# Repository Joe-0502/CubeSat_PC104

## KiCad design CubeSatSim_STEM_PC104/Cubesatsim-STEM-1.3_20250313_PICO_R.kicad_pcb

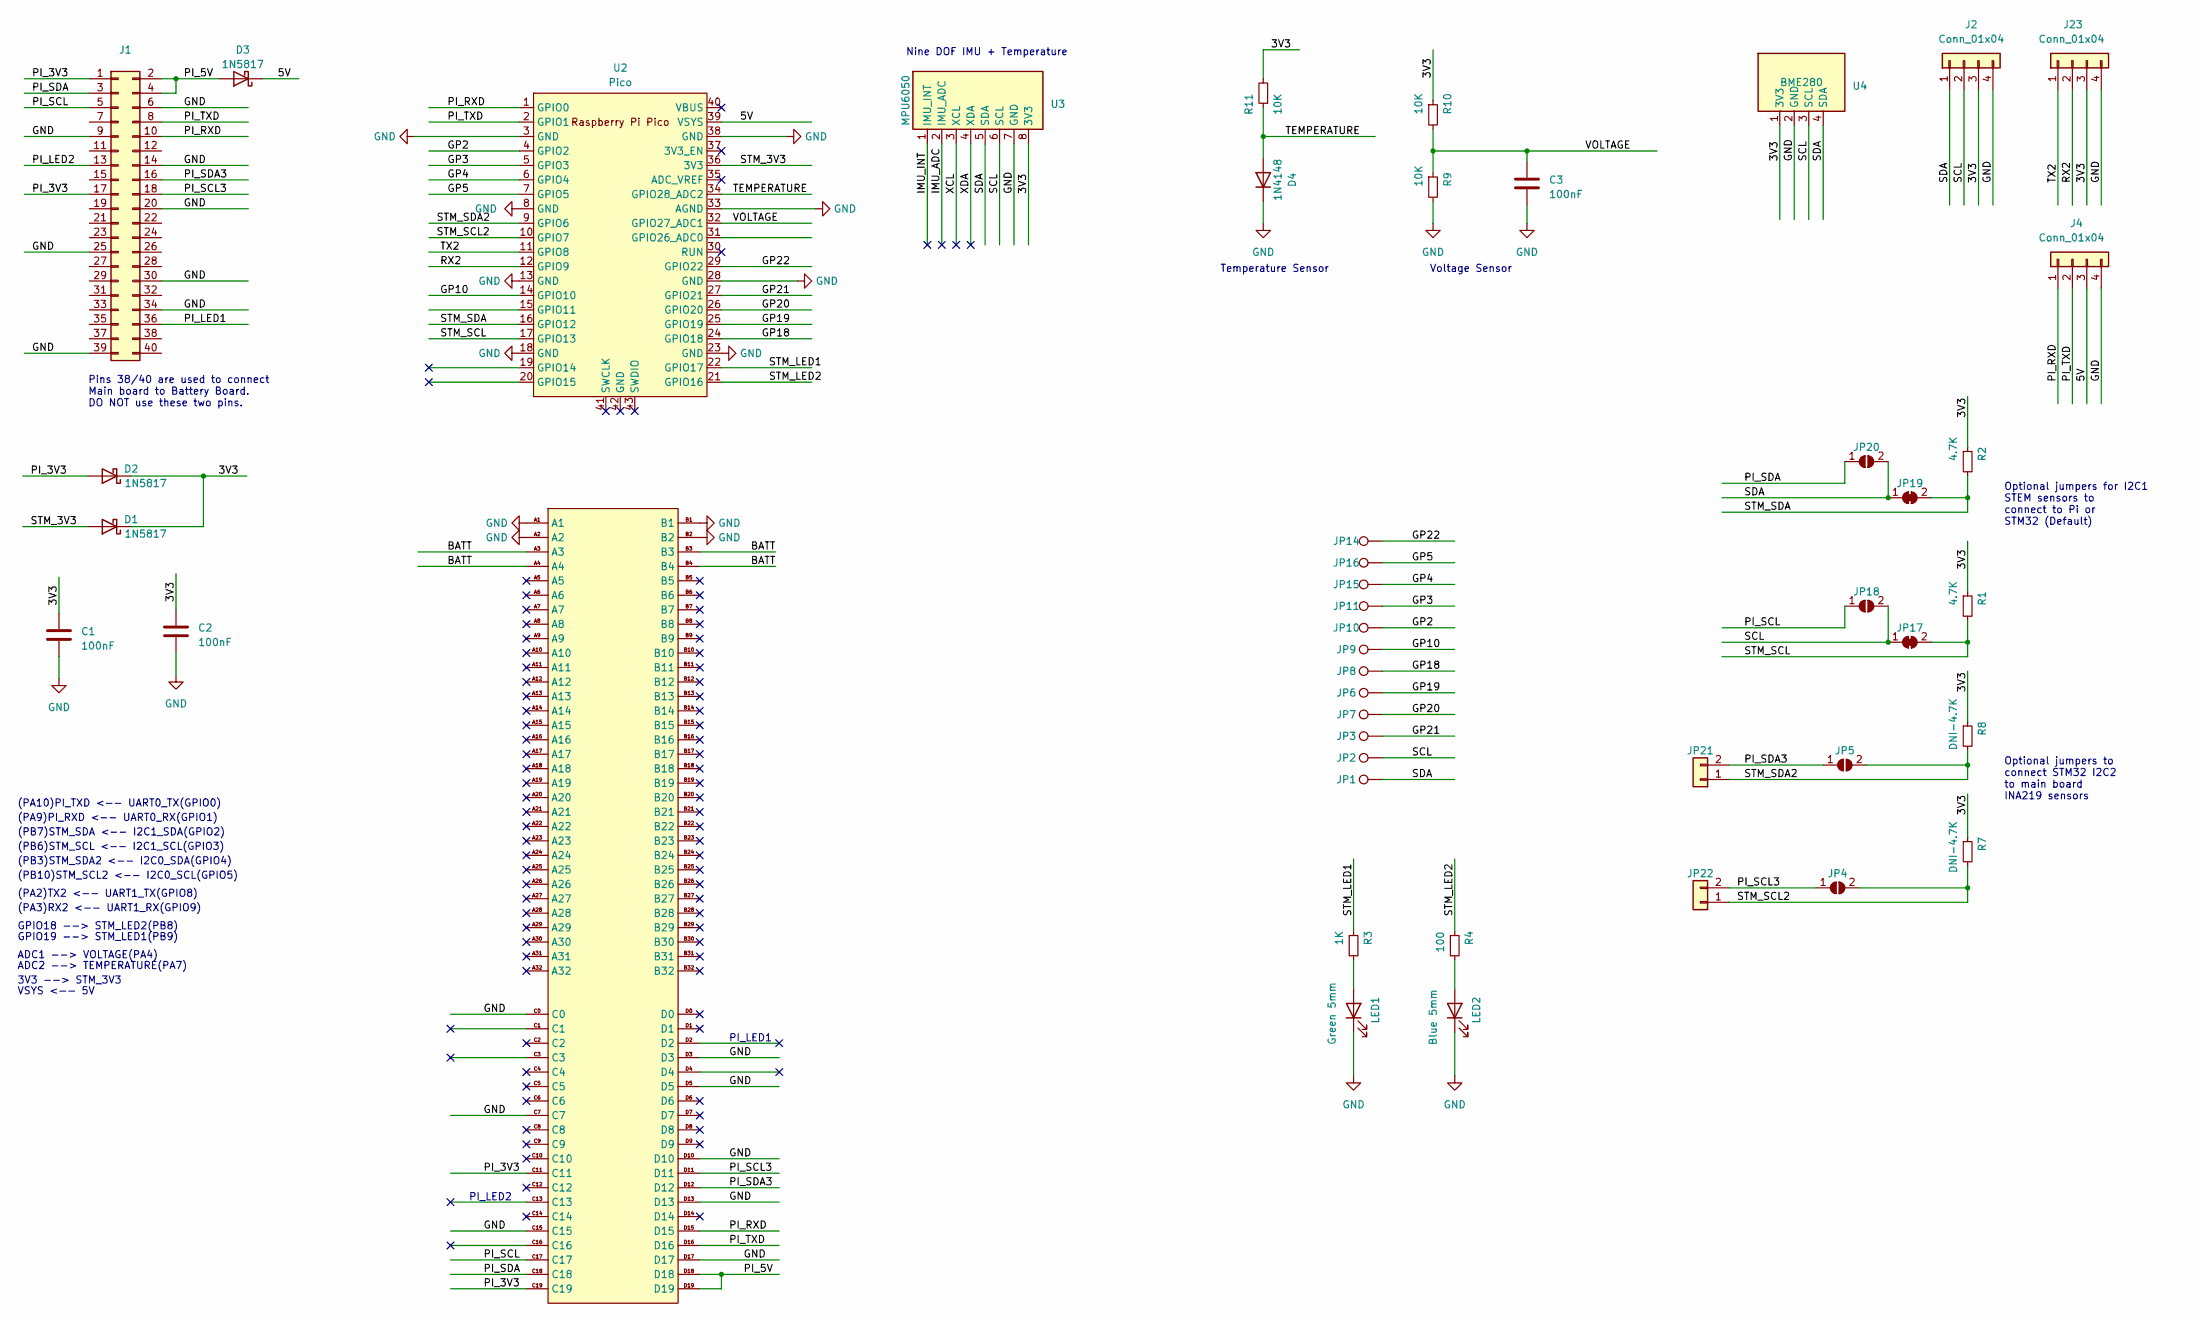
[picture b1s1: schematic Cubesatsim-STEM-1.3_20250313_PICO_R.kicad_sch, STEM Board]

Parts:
C1, C2, C3: 100nF; AMSAT_C_TH_5.08
D1, D2, D3: 1N5817; 1N5817_TH_100mil
D4: 1N4148; 1N5817_TH_100mil
J1: Conn_02x20_Odd_Even; PinHeader_2x20_P2.54mm_Vertical
J2, J4, J23: Conn_01x04; PinHeader_1x04_P2.54mm_Vertical
J3: CubeSat_PC104_16bit_footprint_Edge.Cut
JP1, JP2, JP3, JP6, JP7, JP8, JP9, JP10, JP11, JP14, JP15, JP16: TestPoint; Test_Point_Vertical_S
JP4, JP5, JP18, JP20: SolderJumper_2_Open; SolderJumper-2_P1.3mm_Open_Pad1.0x1.5mm
JP17, JP19: SolderJumper_2_Bridged; SolderJumper-2_P1.3mm_Bridged_Pad1.0x1.5mm
JP21, JP22: Conn_01x02; PinHeader_1x02_P2.54mm_Vertical
LED1: Green 5mm; LED_D3.0mm
LED2: Blue 5mm; LED_D3.0mm
R1, R2: 4.7K; R_TH_V_2.54
R3: 1K; R_TH_V_2.54
R4: 100; R_TH_V_2.54
R7, R8: DNI-4.7K; R_TH_V_2.54
R9, R10, R11: 10K; R_TH_V_2.54
U2: Pico; RPi_Pico_TH
U3: MPU6050; MPU6050_IMU_Module
U4: BME280; BME280_Module

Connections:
/3V3: C1.1, C2.1, D1.1 (K), D2.1 (K), J2.3, J23.3, R1.1, R2.1, R7.1, R8.1, R10.1, R11.2, U3.8 (3V3), U4.1 (3V3)
/5V: D3.1 (K), J4.3, U2.39 (VSYS)
/BATT: J3.A3, J3.A4, J3.B3, J3.B4
/GP2: JP10.1, U2.4 (GPIO2)
/GP3: JP11.1, U2.5 (GPIO3)
/GP4: JP15.1, U2.6 (GPIO4)
/GP5: JP16.1, U2.7 (GPIO5)
/GP10: JP9.1, U2.14 (GPIO10)
/GP18: JP8.1, U2.24 (GPIO18)
/GP19: JP6.1, U2.25 (GPIO19)
/GP20: JP7.1, U2.26 (GPIO20)
/GP21: JP3.1, U2.27 (GPIO21)
/GP22: JP14.1, U2.29 (GPIO22)
/IMU_ADC: U3.2 (IMU_ADC)
/IMU_INT: U3.1 (IMU_INT)
/PI_3V3: D2.2 (A), J1.1, J1.17, J3.C11, J3.C19
/PI_5V: D3.2 (A), J1.2, J1.4, J3.D18, J3.D19
/PI_LED1: J1.36
/PI_LED2: J1.13
/PI_RXD: J1.10, J3.D15, J4.1, U2.1 (GPIO0)
/PI_SCL: J1.5, J3.C17, JP18.1 (A)
/PI_SCL3: J1.18, J3.D11, JP4.1 (A), JP22.2
/PI_SDA: J1.3, J3.C18, JP20.1 (A)
/PI_SDA3: J1.16, J3.D12, JP5.1 (A), JP21.2
/PI_TXD: J1.8, J3.D16, J4.2, U2.2 (GPIO1)
/RX2: J23.2, U2.12 (GPIO9)
/SCL: J2.2, JP2.1, JP17.1 (A), JP18.2 (B), U3.6 (SCL), U4.3 (SCL)
/SDA: J2.1, JP1.1, JP19.1 (A), JP20.2 (B), U3.5 (SDA), U4.4 (SDA)
/STM_3V3: D1.2 (A), U2.36 (3V3)
/STM_LED1: R3.1, U2.22 (GPIO17)
/STM_LED2: R4.1, U2.21 (GPIO16)
/STM_SCL: JP17.2 (B), R1.2, U2.17 (GPIO13)
/STM_SCL2: JP4.2 (B), JP22.1, R7.2, U2.10 (GPIO7)
/STM_SDA: JP19.2 (B), R2.2, U2.16 (GPIO12)
/STM_SDA2: JP5.2 (B), JP21.1, R8.2, U2.9 (GPIO6)
/TEMPERATURE: D4.2 (A), R11.1, U2.34 (GPIO28_ADC2)
/TX2: J23.1, U2.11 (GPIO8)
/VOLTAGE: C3.2, R9.1, R10.2, U2.32 (GPIO27_ADC1)
/XCL: U3.3 (XCL)
/XDA: U3.4 (XDA)
GND: C1.2, C2.2, C3.1, D4.1 (K), J1.6, J1.9, J1.14, J1.20, J1.25, J1.30, J1.34, J1.39, J2.4, J3.A1, J3.A2, J3.B1, J3.B2, J3.C0, J3.C7, J3.C15, J3.D3, J3.D5, J3.D10, J3.D13, J3.D17, J4.4, J23.4, LED1.1 (K), LED2.1 (K), R9.2, U2.3 (GND), U2.8 (GND), U2.13 (GND), U2.18 (GND), U2.23 (GND), U2.28 (GND), U2.33 (AGND), U2.38 (GND), U3.7 (GND), U4.2 (GND)
unnamed: LED1.2 (A), R3.2
unnamed: LED2.2 (A), R4.2

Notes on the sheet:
(PB3)STM_SDA2 <-- I2C0_SDA(GPIO4)
(PB7)STM_SDA <-- I2C1_SDA(GPIO2)
PI_LED2
Temperature Sensor
VSYS <-- 5V
(PA2)TX2 <-- UART1_TX(GPIO8)
3V3 --> STM_3V3
GPIO19 --> STM_LED1(PB9)
Pins 38/40 are used to connect Main board to Battery Board. DO NOT use these two pins.
PI_LED1
Optional jumpers to connect STM32 I2C2 to main board INA219 sensors
(PB6)STM_SCL <-- I2C1_SCL(GPIO3)
(PB10)STM_SCL2 <-- I2C0_SCL(GPIO5)
(PA9)PI_RXD <-- UART0_RX(GPIO1)
Optional jumpers for I2C1 STEM sensors to connect to Pi or STM32 (Default)
(PA10)PI_TXD <-- UART0_TX(GPIO0)
(PA3)RX2 <-- UART1_RX(GPIO9)
ADC2 --> TEMPERATURE(PA7)
GPIO18 --> STM_LED2(PB8)
Voltage Sensor
Nine DOF IMU + Temperature
ADC1 --> VOLTAGE(PA4)

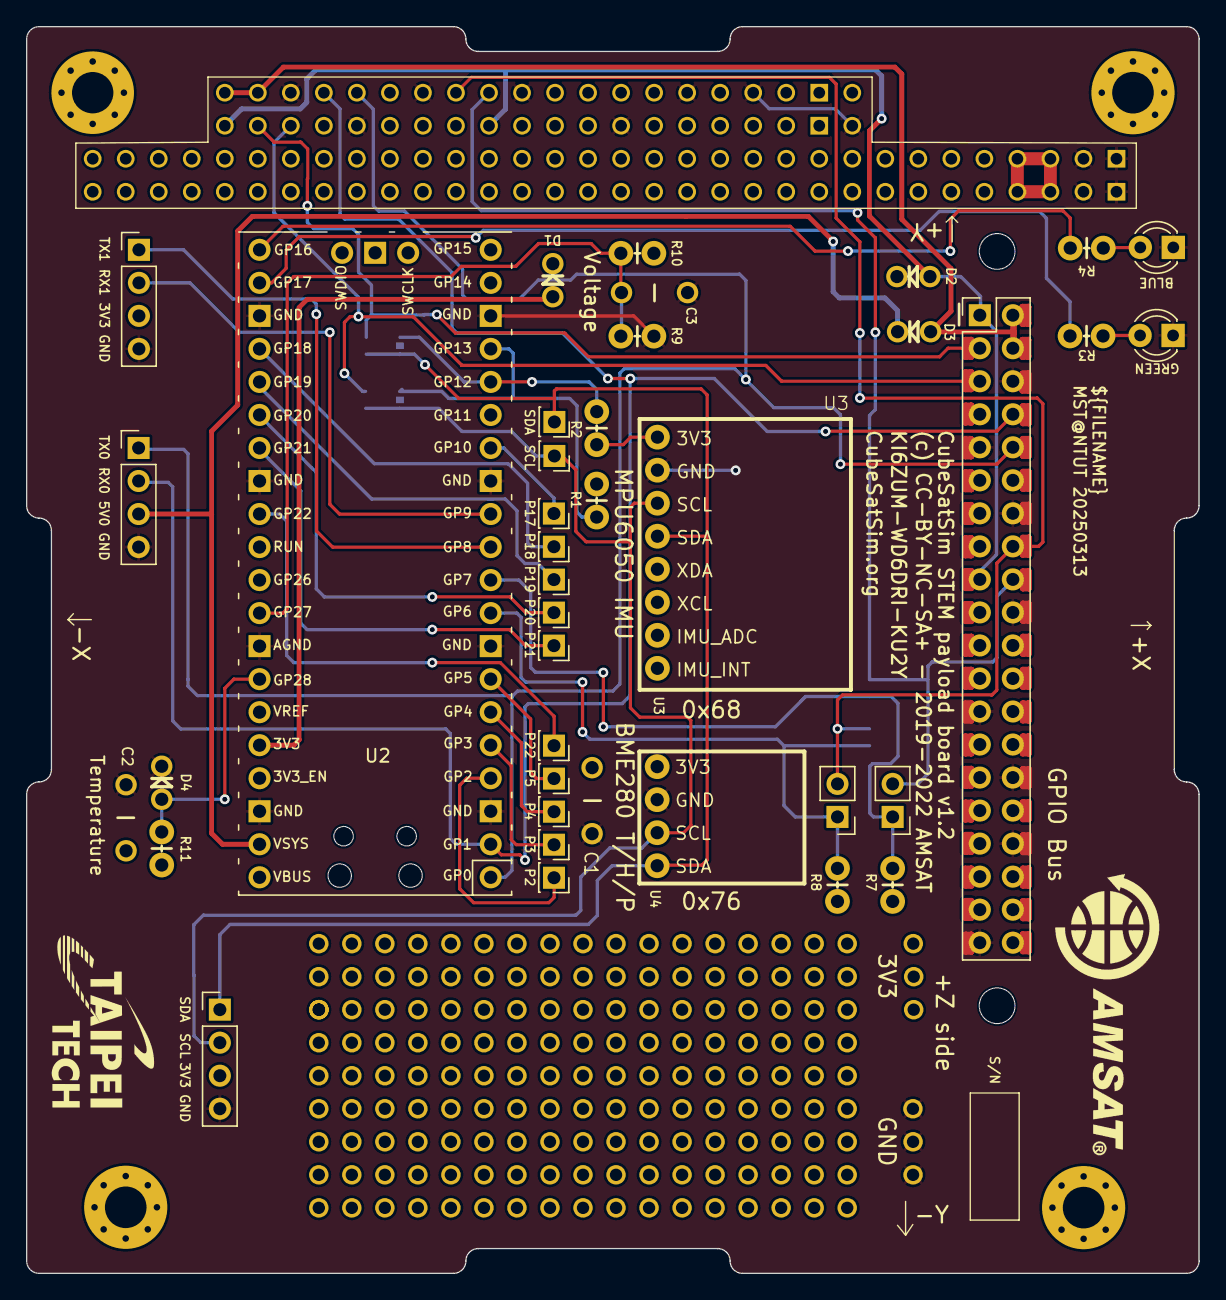
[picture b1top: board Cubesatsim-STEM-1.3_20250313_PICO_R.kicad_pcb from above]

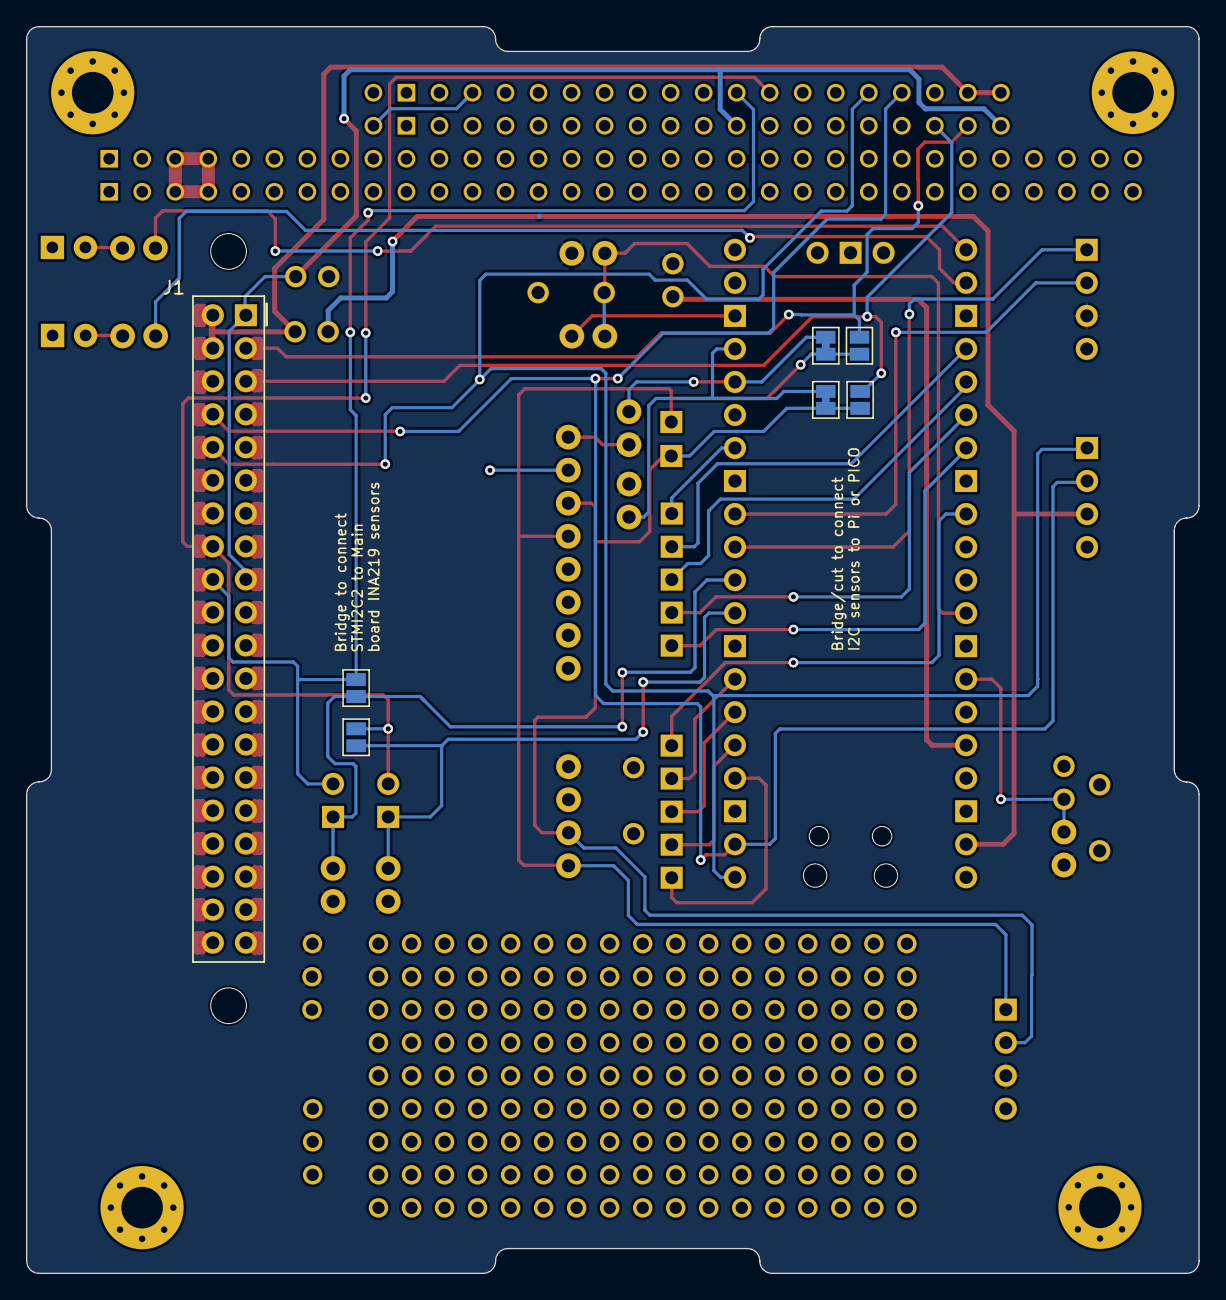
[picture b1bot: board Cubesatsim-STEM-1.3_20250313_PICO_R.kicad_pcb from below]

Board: 2 copper layers, 90.2 x 95.9 mm, 46 parts (6 on the bottom side), 37 nets.

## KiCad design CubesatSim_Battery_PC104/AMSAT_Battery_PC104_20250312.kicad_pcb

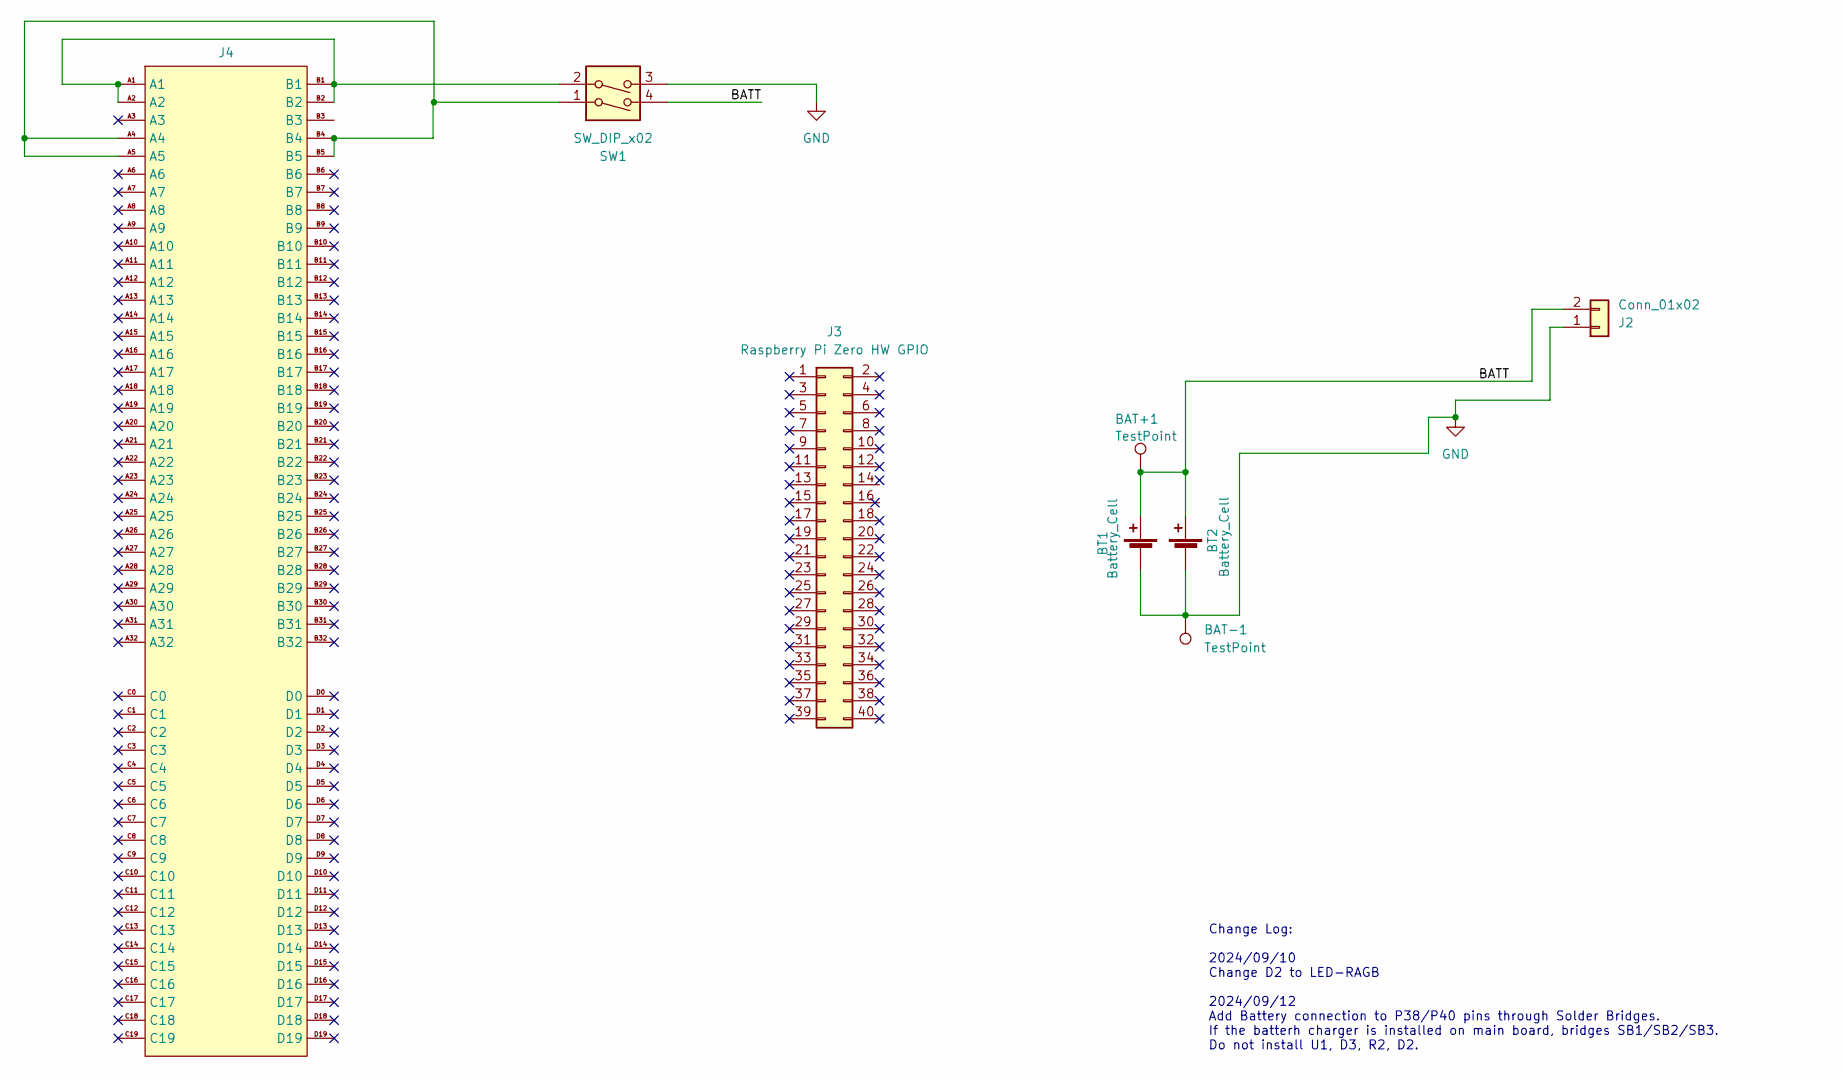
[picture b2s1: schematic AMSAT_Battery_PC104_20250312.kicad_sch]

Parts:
BAT+1: TestPoint; TestPoint_THTPad_2.0x2.0mm_Drill1.0mm
BAT-1: TestPoint; TestPoint_THTPad_2.0x2.0mm_Drill1.0mm
BT1, BT2: Battery_Cell; BatteryHolder_MPD_BH-18650-PC2
J2: Conn_01x02; JST_PH_B2B-PH-K_1x02_P2.00mm_Vertical
J3: Raspberry Pi Zero HW GPIO; PinSocket_2x20_P2.54mm_Vertical
J4: CubeSat_PC104_16bit_footprint_Edge.Cut
SW1: SW_DIP_x02; SW_DIP_SPSTx02_Piano_10.8x6.64mm_W7.62mm_P2.54mm

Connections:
/BATT: BAT+1.1, BT1.1 (+), BT2.1 (+), J2.2, SW1.4
GND: BAT-1.1, BT1.2 (-), BT2.2 (-), J2.1, SW1.3
unnamed: J4.A1, J4.A2, J4.B1, J4.B2, SW1.2
unnamed: J4.A4, J4.A5, J4.B4, J4.B5, SW1.1

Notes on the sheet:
Change Log: 2024/09/10 Change D2 to LED-RAGB 2024/09/12 Add Battery connection to P38/P40 pins through Solder Bridges. If the batterh charger is installed on main board, bridges SB1/SB2/SB3. Do not install U1, D3, R2, D2.

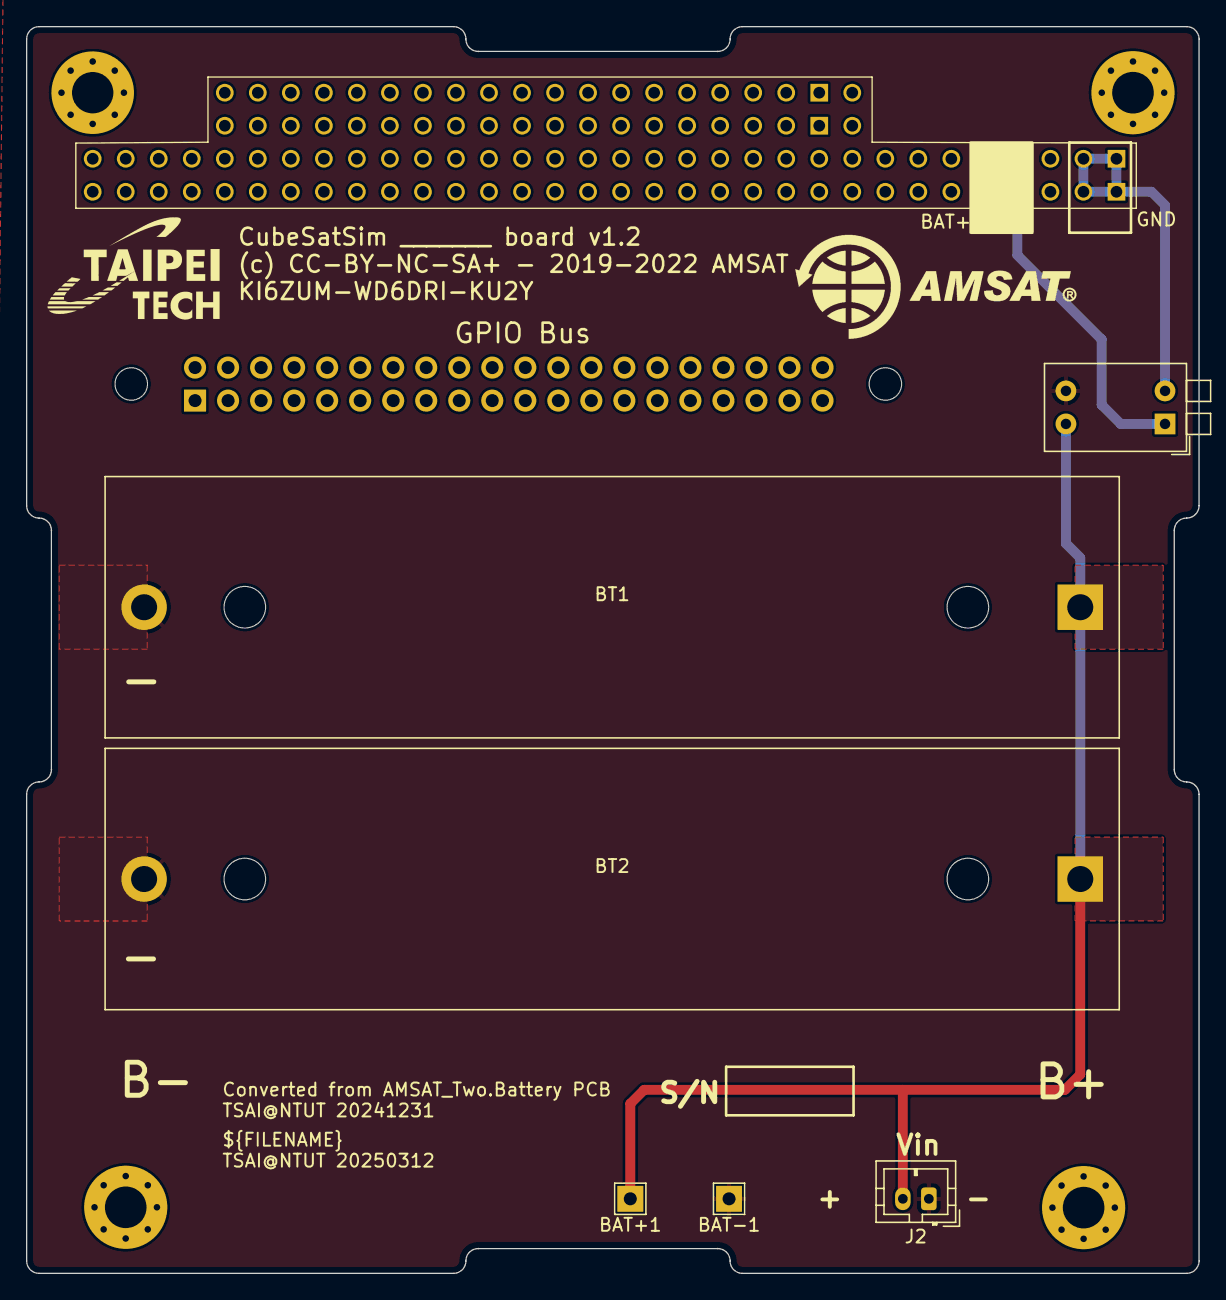
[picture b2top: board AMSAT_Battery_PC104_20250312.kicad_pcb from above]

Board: 2 copper layers, 90.2 x 95.9 mm, 8 parts (1 on the bottom side), 4 nets.

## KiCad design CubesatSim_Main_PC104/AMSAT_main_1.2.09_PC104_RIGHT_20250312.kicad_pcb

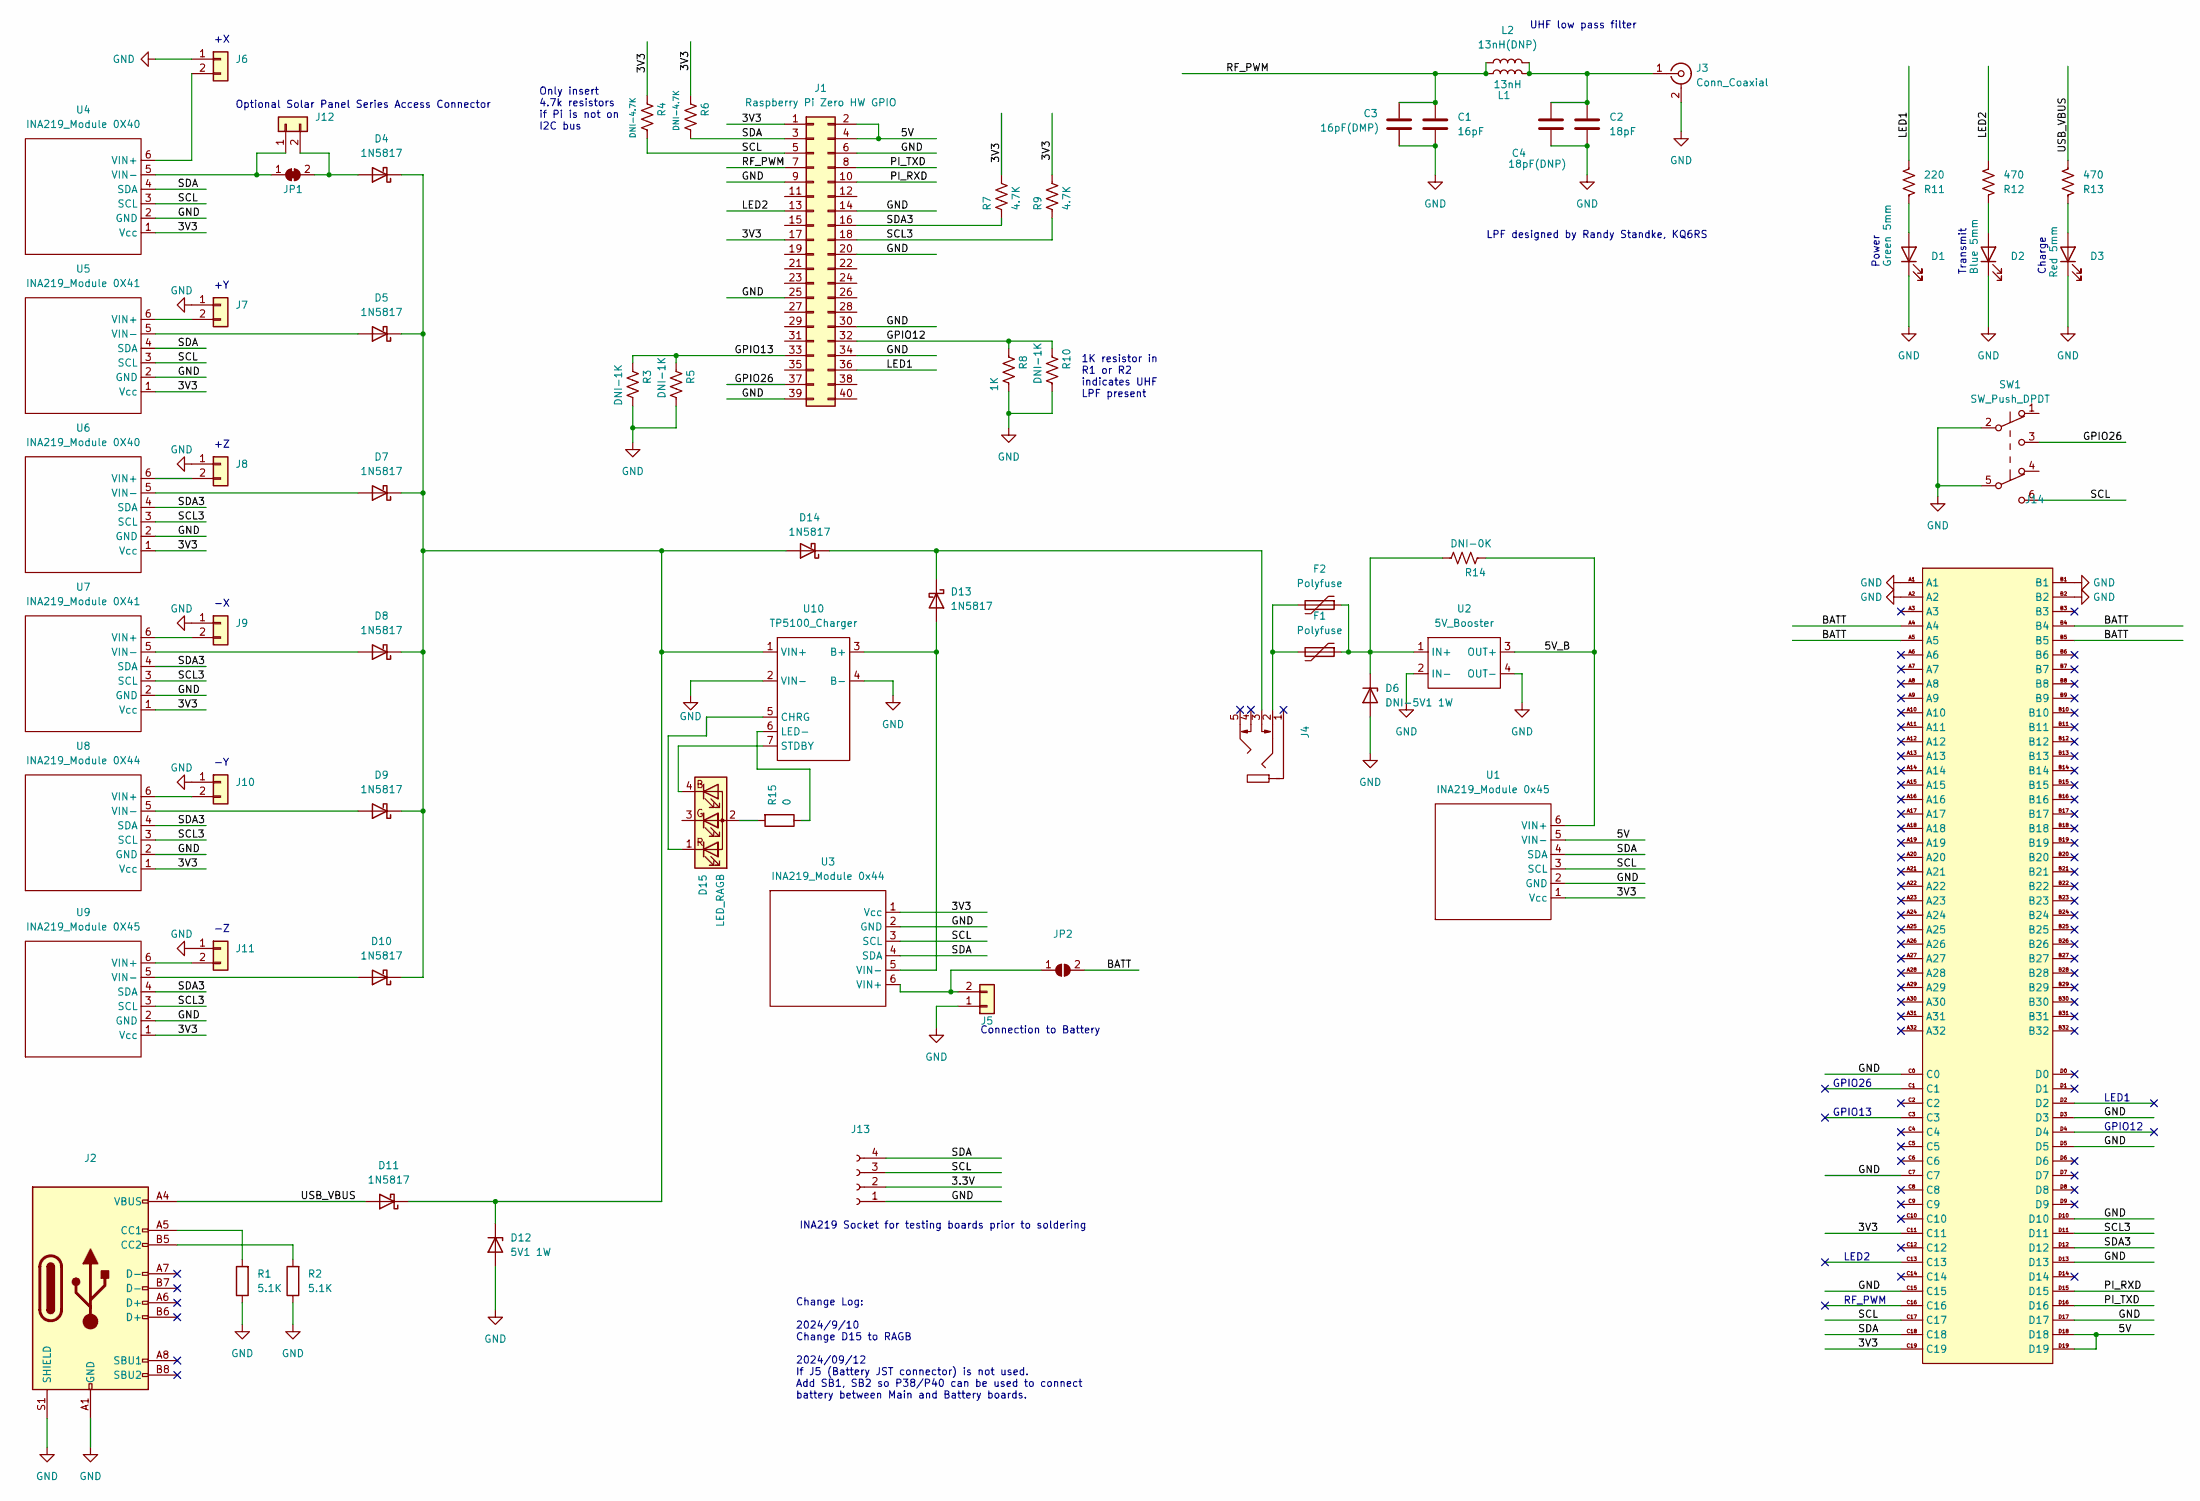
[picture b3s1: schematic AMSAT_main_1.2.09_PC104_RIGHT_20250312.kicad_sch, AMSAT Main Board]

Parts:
C1: 16pF; C_0603_1608Metric
C2: 18pF; C_0603_1608Metric
C3: 16pF(DMP); C_0402_1005Metric
C4: 18pF(DNP); C_0402_1005Metric
D1: Green 5mm; LED_D5.0mm
D2: Blue 5mm; LED_D5.0mm
D3: Red 5mm; LED_D5.0mm
D4, D5, D7, D8, D9, D10, D11, D13, D14: 1N5817; SS14
D6: DNI-5V1 1W; 1N5817
D12: 5V1 1W; 1N5817
D15: LED_RAGB; LED_D5.0mm-4_RGB
F1: Polyfuse; Fuse_1812_4532Metric
F2: Polyfuse; AMSAT_PTC
J1: Raspberry Pi Zero HW GPIO; PinSocket_2x20_P2.54mm_Vertical
J2: USB_C_Receptacle_USB2.0; USB_C_Receptacle_GCT_USB4105-xx-A_16P_TopMnt_Horizontal
J3: Conn_Coaxial; AMSAT_SMA_Vertical
J4: AudioJack2_Dual_Ground_Switch; Jack_3.5mm_CUI_SJ1-3525N_Horizontal
J5, J6, J7, J8, J9, J10, J11, J12: Conn_01x02; JST_PH_B2B-PH-K_1x02_P2.00mm_Vertical
J13: Conn_01x04_Female; PinHeader_1x04_P2.54mm_Vertical
J14: CubeSat_PC104_16bit_footprint_Edge.Cut
JP1: SolderJumper_2_Bridged; SolderJumper-2_P1.3mm_Bridged_Pad1.0x1.5mm
JP2: SolderJumper_2_Open; SolderJumper_2_Tri_New
L1: 13nH; L_0603_1608Metric
L2: 13nH(DNP); L_0402_1005Metric
R1, R2: 5.1K; R_0603_1608Metric
R3: DNI-1K; R_Axial_DIN0204_L3.6mm_D1.6mm_P2.54mm_Vertical
R4, R6: DNI-4.7K; R_Axial_DIN0204_L3.6mm_D1.6mm_P2.54mm_Vertical
R5, R10: DNI-1K; R_0603_1608Metric
R7, R9: 4.7K; R_Axial_DIN0204_L3.6mm_D1.6mm_P2.54mm_Vertical
R8: 1K; R_Axial_DIN0204_L3.6mm_D1.6mm_P2.54mm_Vertical
R11: 220; R_Axial_DIN0204_L3.6mm_D1.6mm_P2.54mm_Vertical
R12, R13: 470; R_Axial_DIN0204_L3.6mm_D1.6mm_P2.54mm_Vertical
R14: DNI-0K; R_0805_2012Metric
R15: 0; R_0603_1608Metric
SW1: SW_Push_DPDT; SW_Push_2P2T_Vertical_E-Switch_800UDP8P1A1M6
U1: INA219_Module 0x45; INA219_Small
U2: 5V_Booster; 5V_BOOSTER
U3: INA219_Module 0x44; INA219_Small
U4, U6: INA219_Module 0X40; INA219_Small
U5, U7: INA219_Module 0X41; INA219_Small
U8: INA219_Module 0X44; INA219_Small
U9: INA219_Module 0X45; INA219_Small
U10: TP5100_Charger; TP5100 Charger_SMD

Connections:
/3.3V: J13.2
/3V3: J1.1, J1.17, J14.C11, J14.C19, R4.1, R6.1, R7.1, R9.1, U1.1 (Vcc), U3.1 (Vcc), U4.1 (Vcc), U5.1 (Vcc), U6.1 (Vcc), U7.1 (Vcc), U8.1 (Vcc), U9.1 (Vcc)
/5V: J1.2, J1.4, J14.D18, J14.D19, U1.5 (VIN-)
/5V_B: R14.1, U1.6 (VIN+), U2.3 (OUT+)
/BATT: J14.A4, J14.A5, J14.B4, J14.B5, JP2.2 (B)
/GPIO12: J1.32, R8.1, R10.1
/GPIO13: J1.33, R3.1, R5.1
/GPIO26: J1.37, SW1.3 (C)
/LED1: J1.36, R11.2
/LED2: J1.13, R12.2
/PI_RXD: J1.10, J14.D15
/PI_TXD: J1.8, J14.D16
/RF_PWM: C1.1, C3.1, J1.7, L1.1, L2.1
/SCL: J1.5, J13.3, J14.C17, R4.2, SW1.6 (C), U1.3 (SCL), U3.3 (SCL), U4.3 (SCL), U5.3 (SCL)
/SCL3: J1.18, J14.D11, R9.2, U6.3 (SCL), U7.3 (SCL), U8.3 (SCL), U9.3 (SCL)
/SDA: J1.3, J13.4, J14.C18, R6.2, U1.4 (SDA), U3.4 (SDA), U4.4 (SDA), U5.4 (SDA)
/SDA3: J1.16, J14.D12, R7.2, U6.4 (SDA), U7.4 (SDA), U8.4 (SDA), U9.4 (SDA)
/USB_VBUS: D11.2 (A), J2.A4 (VBUS), J2.A9 (VBUS), J2.B4 (VBUS), J2.B9 (VBUS), R13.2; also elsewhere on the board
GND: C1.2, C2.2, C3.2, C4.2, D1.1 (K), D2.1 (K), D3.1 (K), D6.2 (A), D12.2 (A), J1.6, J1.9, J1.14, J1.20, J1.25, J1.30, J1.34, J1.39, J2.A1 (GND), J2.A12 (GND), J2.B1 (GND), J2.B12 (GND), J2.S1 (SHIELD), J3.2 (Ext), J5.1, J6.1, J7.1, J8.1, J9.1, J10.1, J11.1, J13.1, J14.A1, J14.A2, J14.B1, J14.B2, J14.C0, J14.C7, J14.C15, J14.D3, J14.D5, J14.D10, J14.D13, J14.D17, R1.1, R2.1, R3.2, R5.2, R8.2, R10.2, SW1.2 (B), SW1.5 (B), U1.2 (GND), U2.2 (IN-), U2.4 (OUT-), U3.2 (GND), U4.2 (GND), U5.2 (GND), U6.2 (GND), U7.2 (GND), U8.2 (GND), U9.2 (GND), U10.2 (VIN-), U10.4 (B-); also elsewhere on the board
unnamed: D1.2 (A), R11.1
unnamed: D2.2 (A), R12.1
unnamed: D3.2 (A), R13.1
unnamed: D4.2 (A), J12.2, JP1.2 (B)
unnamed: D5.2 (A), U5.5 (VIN-)
unnamed: D6.1 (K), F1.1, F2.1, R14.2, U2.1 (IN+)
unnamed: D7.2 (A), U6.5 (VIN-)
unnamed: D8.2 (A), U7.5 (VIN-)
unnamed: D9.2 (A), U8.5 (VIN-)
unnamed: D10.2 (A), U9.5 (VIN-)
unnamed: D4.1 (K), D5.1 (K), D7.1 (K), D8.1 (K), D9.1 (K), D10.1 (K), D11.1 (K), D12.1 (K), D14.2 (A), U10.1 (VIN+)
unnamed: D13.2 (A), U3.5 (VIN-), U10.3 (B+)
unnamed: D13.1 (K), D14.1 (K), J4.3
unnamed: D15.2 (A), R15.2
unnamed: D15.4 (BK), U10.7 (STDBY)
unnamed: D15.1 (RK), U10.5 (CHRG)
unnamed: F1.2, F2.2, J4.2
unnamed: J2.A5 (CC1), R1.2
unnamed: J2.B5 (CC2), R2.2
unnamed: C2.1, C4.1, J3.1 (In), L1.2, L2.2
unnamed: J5.2, JP2.1 (A), U3.6 (VIN+)
unnamed: J6.2, U4.6 (VIN+)
unnamed: J7.2, U5.6 (VIN+)
unnamed: J8.2, U6.6 (VIN+)
unnamed: J9.2, U7.6 (VIN+)
unnamed: J10.2, U8.6 (VIN+)
unnamed: J11.2, U9.6 (VIN+)
unnamed: J12.1, JP1.1 (A), U4.5 (VIN-)
unnamed: R15.1, U10.6 (LED-)

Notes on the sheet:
GPIO26
Power
Change Log: 2024/9/10 Change D15 to RAGB 2024/09/12 If J5 (Battery JST connector) is not used. Add SB1, SB2 so P38/P40 can be used to connect battery between Main and Battery boards.
LED1
LPF designed by Randy Standke, KQ6RS
UHF low pass filter
RF_PWM
Optional Solar Panel Series Access Connector
Transmit
INA219 Socket for testing boards prior to soldering
LED2
GPIO12
1K resistor in R1 or R2 indicates UHF LPF present
Only insert 4.7k resistors if Pi is not on I2C bus
Charge
Connection to Battery
GPIO13

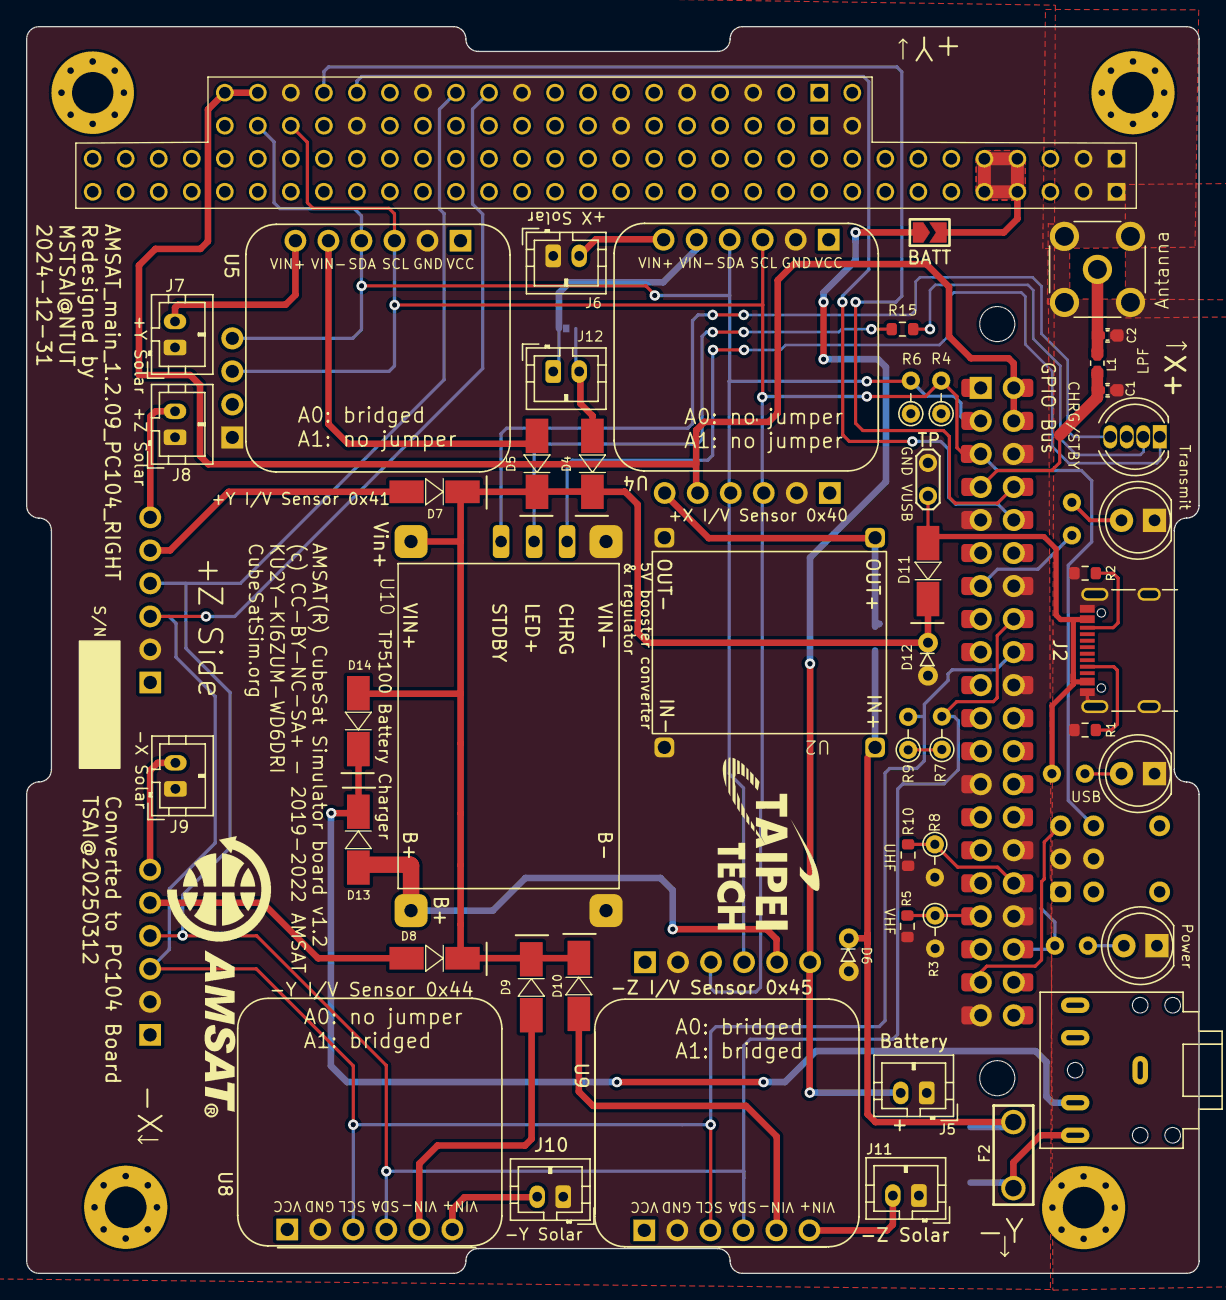
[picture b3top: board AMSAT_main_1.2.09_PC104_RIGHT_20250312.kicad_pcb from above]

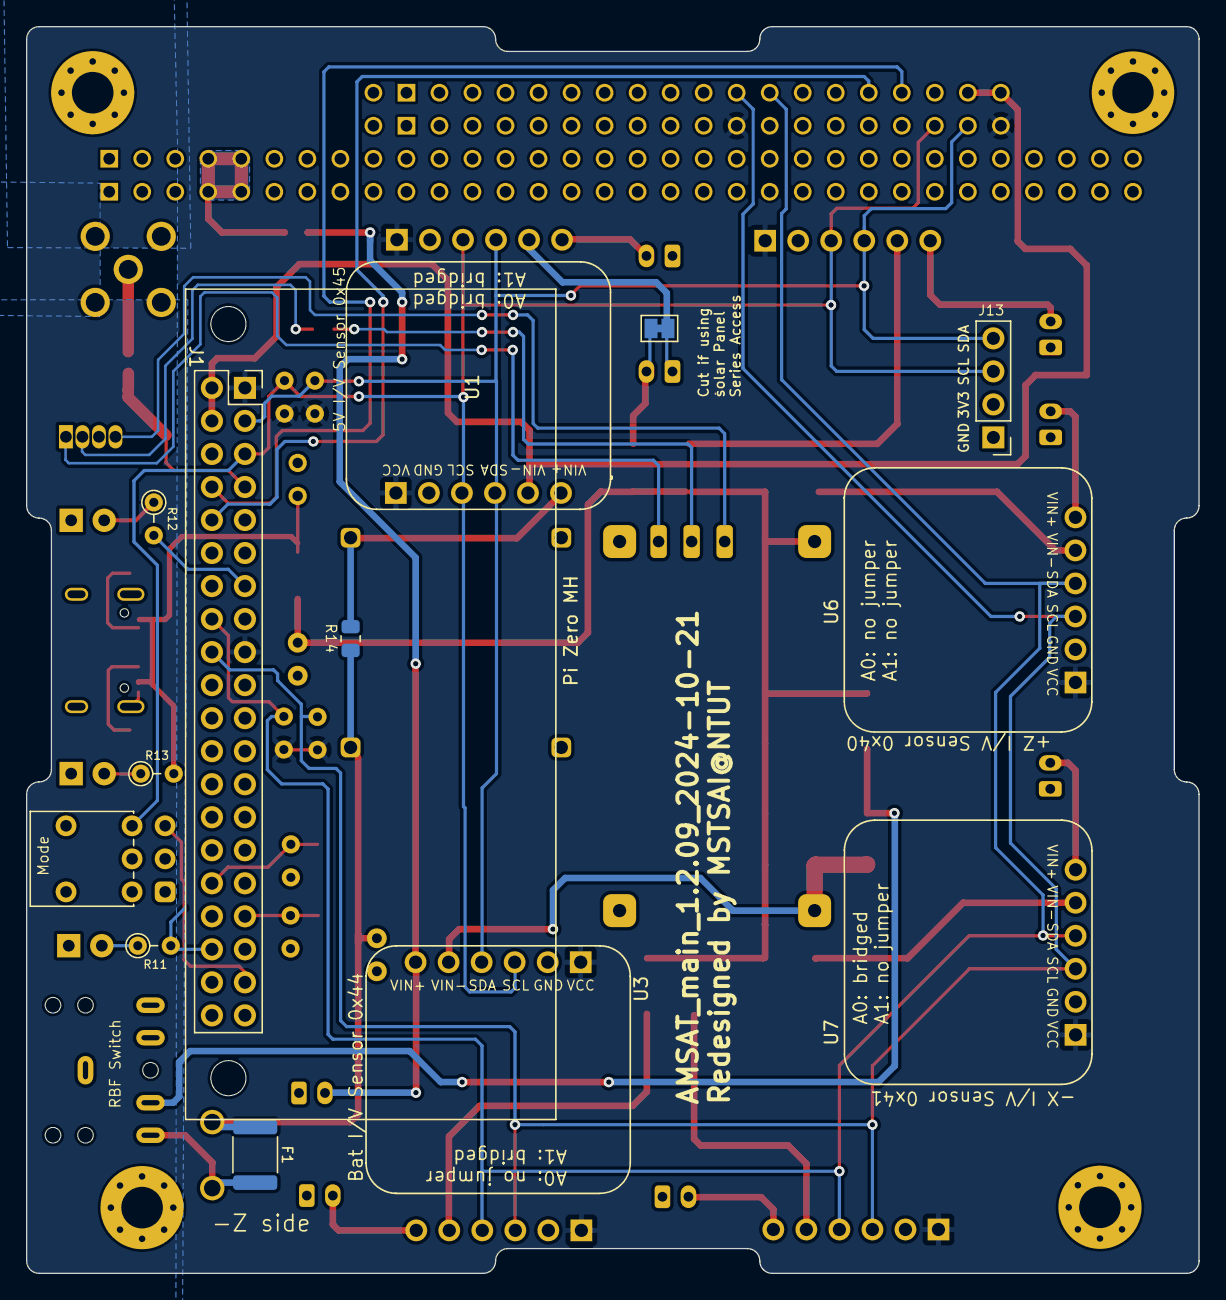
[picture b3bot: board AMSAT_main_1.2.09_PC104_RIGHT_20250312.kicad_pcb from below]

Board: 2 copper layers, 90.2 x 95.9 mm, 66 parts (13 on the bottom side), 47 nets.

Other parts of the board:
TP: TestPoint_2Pads_Pitch2.54mm_Drill0.8mm

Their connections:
/USB_VBUS: TP.1; also elsewhere on the board
GND: TP.2; also elsewhere on the board

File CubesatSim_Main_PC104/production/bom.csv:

Designator,Footprint,Quantity,Value,LCSC Part #
"_41, _40, _39, _38, _37, _36, _35, _34, _33, _32, _31, _30, _29, _28, _27, _26, _25, _24, _23, _22, _21, _20, _19, _18, _17, _16, _15, _14, _13, _12, _11, _10, _9, _8, _7, _6, _5, _4, _3, _2, ",,41,,
C1,0603,1,16pF,
C2,0603,1,18pF,
C3,0402,1,16pF(DMP),
C4,0402,1,18pF(DNP),
D1,LED_D5.0mm,1,Green 5mm,
"D10, D11, D13, D14, D4, D5, D7, D8, D9",SS14,9,1N5817,
D12,1N5817,1,5V1 1W,
D15,LED_D5.0mm-4_RGB,1,LED_RAGB,
D2,LED_D5.0mm,1,Blue 5mm,
D3,LED_D5.0mm,1,Red 5mm,
D6,1N5817,1,DNI-5V1 1W,
F1,1812,1,Polyfuse,
F2,AMSAT_PTC,1,Polyfuse,
J1,PinSocket_2x20_P2.54mm_Vertical,1,Raspberry Pi Zero HW GPIO,
"J10, J11, J12, J5, J6, J7, J8, J9",JST_PH_B2B-PH-K_1x02_P2.00mm_Vertical,8,Conn_01x02,
J13,PinHeader_1x04_P2.54mm_Vertical,1,Conn_01x04_Female,
J14,CubeSat_PC104_16bit_footprint_Edge.Cut,1,~,
J2,USB_C_Receptacle_GCT_USB4105-xx-A_16P_TopMnt_Horizontal,1,USB_C_Receptacle_USB2.0,
J3,AMSAT_SMA_Vertical,1,Conn_Coaxial,
J4,Jack_3.5mm_CUI_SJ1-3525N_Horizontal,1,AudioJack2_Dual_Ground_Switch,
JP1,SolderJumper-2_P1.3mm_Bridged_Pad1.0x1.5mm,1,SolderJumper_2_Bridged,
JP2,SolderJumper_2_Tri_New,1,SolderJumper_2_Open,
L1,0603,1,13nH,
L2,0402,1,13nH(DNP),
"R1, R2",0603,2,5.1K,
"R10, R5",0603,2,DNI-1K,
R11,R_Axial_DIN0204_L3.6mm_D1.6mm_P2.54mm_Vertical,1,220,
"R12, R13",R_Axial_DIN0204_L3.6mm_D1.6mm_P2.54mm_Vertical,2,470,
R14,0805,1,DNI-0K,
R15,0603,1,0,
R3,R_Axial_DIN0204_L3.6mm_D1.6mm_P2.54mm_Vertical,1,DNI-1K,
"R4, R6",R_Axial_DIN0204_L3.6mm_D1.6mm_P2.54mm_Vertical,2,DNI-4.7K,
"R7, R9",R_Axial_DIN0204_L3.6mm_D1.6mm_P2.54mm_Vertical,2,4.7K,
R8,R_Axial_DIN0204_L3.6mm_D1.6mm_P2.54mm_Vertical,1,1K,
SW1,SW_Push_2P2T_Vertical_E-Switch_800UDP8P1A1M6,1,SW_Push_DPDT,
"U1, U9",INA219_Small,2,INA219_Module 0x45,
U10,TP5100 Charger_SMD,1,TP5100_Charger,
U2,5V_BOOSTER,1,5V_Booster,
"U3, U8",INA219_Small,2,INA219_Module 0x44,
"U4, U6",INA219_Small,2,INA219_Module 0X40,
"U5, U7",INA219_Small,2,INA219_Module 0X41,

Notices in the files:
CubeSatSim_STEM_PC104/Cubesatsim-STEM-1.3_20250313_PICO_R.kicad_pcb:
(c) CC-BY-NC-SA+ - 2019-2022 AMSAT
